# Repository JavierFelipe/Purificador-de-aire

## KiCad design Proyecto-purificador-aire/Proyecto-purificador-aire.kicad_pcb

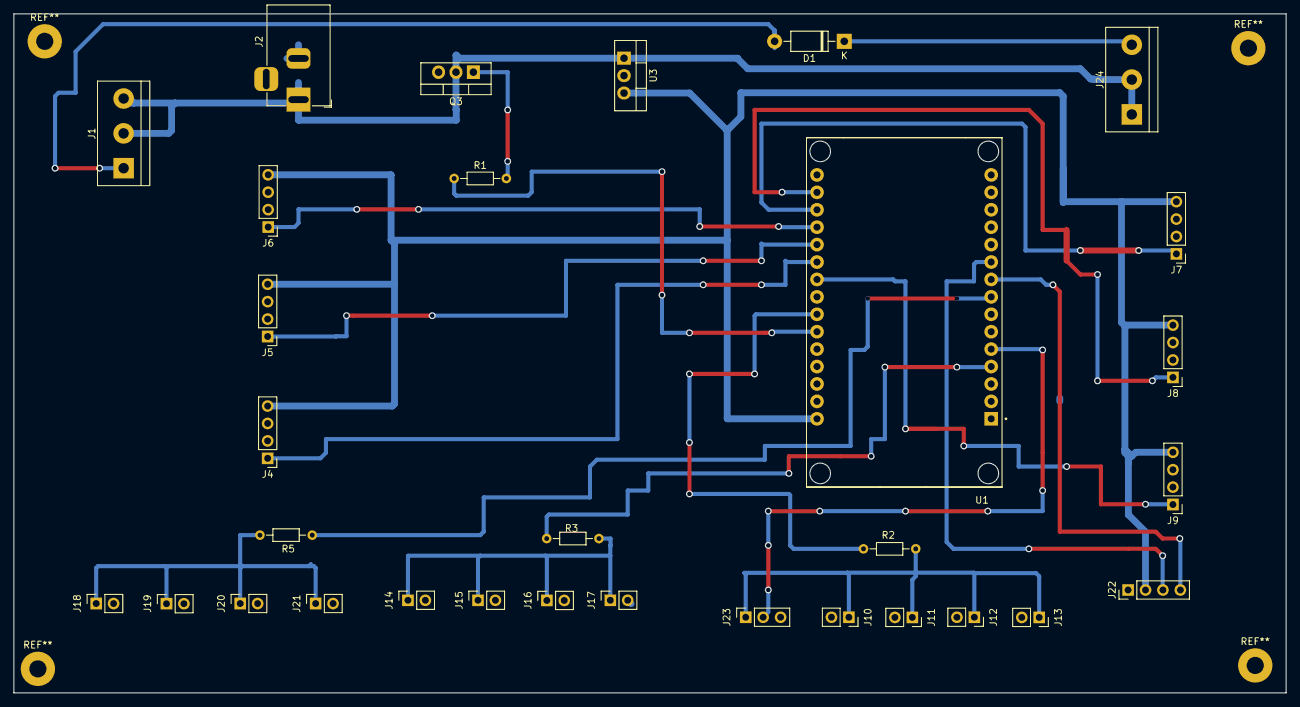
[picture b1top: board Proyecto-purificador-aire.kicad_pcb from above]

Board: 2 copper layers, 185.5 x 99.0 mm, 31 parts (0 on the bottom side), 22 nets.

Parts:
D1: 1N4007; D_DO-41_SOD81_P10.16mm_Horizontal
J1, J24: Screw_Terminal_01x03; TerminalBlock_bornier-3_P5.08mm
J2: Barrel_Jack_Switch; BarrelJack_Horizontal
J4: Sensor 3; PinHeader_1x04_P2.54mm_Vertical
J5: Sensor 2; PinHeader_1x04_P2.54mm_Vertical
J6: Sensor 1; PinHeader_1x04_P2.54mm_Vertical
J7: Sensor 4; PinHeader_1x04_P2.54mm_Vertical
J8: Sensor 5; PinHeader_1x04_P2.54mm_Vertical
J9: Sensor 6; PinHeader_1x04_P2.54mm_Vertical
J10: Luz roja 1; PinSocket_1x02_P2.54mm_Vertical
J11: Luz roja 2; PinSocket_1x02_P2.54mm_Vertical
J12: Luz roja 3; PinSocket_1x02_P2.54mm_Vertical
J13: Luz roja 4; PinSocket_1x02_P2.54mm_Vertical
J14: Luz amarilla 4; PinSocket_1x02_P2.54mm_Vertical
J15: Luz amarilla 1; PinSocket_1x02_P2.54mm_Vertical
J16: Luz amarilla 2; PinSocket_1x02_P2.54mm_Vertical
J17: Luz amarilla 3; PinSocket_1x02_P2.54mm_Vertical
J18: Luz verde 4; PinSocket_1x02_P2.54mm_Vertical
J19: Luz verde 1; PinSocket_1x02_P2.54mm_Vertical
J20: Luz verde 2; PinSocket_1x02_P2.54mm_Vertical
J21: Luz verde 3; PinSocket_1x02_P2.54mm_Vertical
J22: Pantalla OLED; PinHeader_1x04_P2.54mm_Vertical
J23: Buzzer pasivo; PinSocket_1x03_P2.54mm_Vertical
Q3: IRLZ44N; TO-220-3_Vertical
R1, R2, R3, R5: 220R; R_Axial_DIN0204_L3.6mm_D1.6mm_P7.62mm_Horizontal
U1: ESP32-DEVKIT-V1; MODULE_ESP32_DEVKIT_V1
U3: L7805; TO-220-3_Vertical

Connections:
+5V: J4.4, J5.4, J6.4, J7.4, J8.4, J9.4, J22.2, U1.30 (VIN), U3.3 (OUT)
+12V: J1.2, J1.3, J2.1, J24.1, J24.2, Q3.2 (D), U3.1 (IN)
/1a: J6.1, U1.19 (D34)
/1b: J5.1, U1.20 (D35)
/1c: J4.1, U1.21 (D32)
/1d: J7.1, U1.18 (VN)
/1e: J8.1, U1.17 (VP)
/1f: J9.1, U1.22 (D33)
/1g: R2.1, U1.24 (D26)
/1h: R3.1, U1.4 (D2)
/1i: R5.1, U1.8 (D5)
/Mosfet: R1.1, U1.25 (D27)
/SCL: J22.3, U1.10 (D19)
/SDA: J22.4, U1.9 (D18)
/buzzer: J23.2, U1.5 (D4)
GND: J2.2, J2.3, J4.3, J5.3, J6.3, J7.3, J8.3, J9.3, J10.2, J11.2, J12.2, J13.2, J14.2, J15.2, J16.2, J17.2, J18.2, J19.2, J20.2, J21.2, J22.1, J23.3, Q3.3 (S), U1.2 (GND), U1.29 (GND), U3.2 (GND)
unnamed: D1.2 (A), J1.1
unnamed: D1.1 (K), J24.3
unnamed: J10.1, J11.1, J12.1, J13.1, J23.1, R2.2
unnamed: J14.1, J15.1, J16.1, J17.1, R3.2
unnamed: J18.1, J19.1, J20.1, J21.1, R5.2
unnamed: Q3.1 (G), R1.2

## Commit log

2025-03-07 Código
2025-03-08 Cambios
    Se agrego el diseño de la PCB en kicad
2025-03-08 Agreagar código
    Se agregó el código general
2025-03-08 Cambio de nombre
2025-03-08 Nuevos cambios
